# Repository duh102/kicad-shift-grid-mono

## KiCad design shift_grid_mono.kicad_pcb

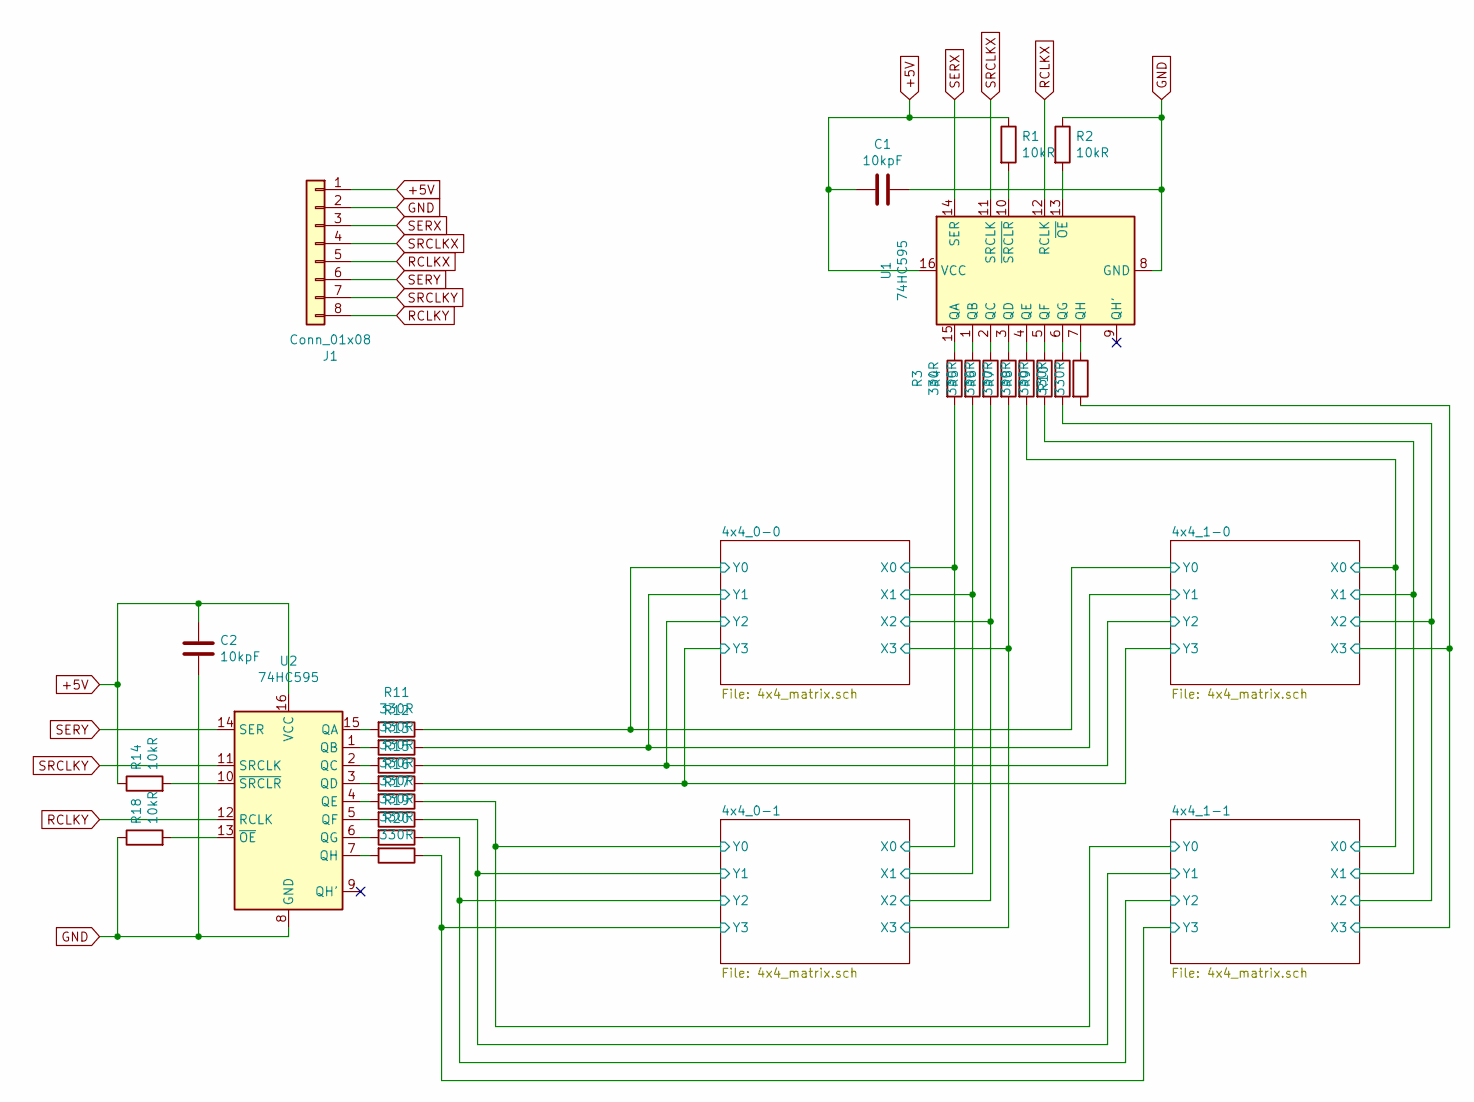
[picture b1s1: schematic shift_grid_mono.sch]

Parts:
C1, C2: 10kpF; C_0805_2012Metric
J1: Conn_01x08; PinHeader_1x08_P2.54mm_Vertical
R1, R2, R14, R18: 10kR; R_0805_2012Metric
R3, R4, R5, R6, R7, R8, R9, R10, R11, R12, R13, R15, R16, R17, R19, R20: 330R; R_0805_2012Metric
U1, U2: 74HC595; SOIC-16_3.9x9.9mm_P1.27mm

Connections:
+5V: C1.2, C2.1, J1.1, R1.1, R14.1, U1.16 (VCC), U2.16 (VCC)
/4x4_0-0/X0: R3.2; also elsewhere on the board
/4x4_0-0/X1: R4.2; also elsewhere on the board
/4x4_0-0/X2: R5.2; also elsewhere on the board
/4x4_0-0/X3: R6.2; also elsewhere on the board
/4x4_0-0/Y0: R11.1; also elsewhere on the board
/4x4_0-0/Y1: R12.1; also elsewhere on the board
/4x4_0-0/Y2: R13.1; also elsewhere on the board
/4x4_0-0/Y3: R15.1; also elsewhere on the board
/4x4_0-1/Y0: R16.1; also elsewhere on the board
/4x4_0-1/Y1: R17.1; also elsewhere on the board
/4x4_0-1/Y2: R19.1; also elsewhere on the board
/4x4_0-1/Y3: R20.1; also elsewhere on the board
/4x4_1-0/X0: R7.2; also elsewhere on the board
/4x4_1-0/X1: R8.2; also elsewhere on the board
/4x4_1-0/X2: R9.2; also elsewhere on the board
/4x4_1-0/X3: R10.2; also elsewhere on the board
GND: C1.1, C2.2, J1.2, R2.1, R18.1, U1.8 (GND), U2.8 (GND)
unnamed: R1.2, U1.10 (~SRCLR)
unnamed: R2.2, U1.13 (~OE)
unnamed: R3.1, U1.15 (QA)
unnamed: R4.1, U1.1 (QB)
unnamed: R5.1, U1.2 (QC)
unnamed: R6.1, U1.3 (QD)
unnamed: R7.1, U1.4 (QE)
unnamed: R8.1, U1.5 (QF)
unnamed: R9.1, U1.6 (QG)
unnamed: R10.1, U1.7 (QH)
unnamed: R11.2, U2.15 (QA)
unnamed: R12.2, U2.1 (QB)
unnamed: R13.2, U2.2 (QC)
unnamed: R14.2, U2.10 (~SRCLR)
unnamed: R15.2, U2.3 (QD)
unnamed: R16.2, U2.4 (QE)
unnamed: R17.2, U2.5 (QF)
unnamed: R18.2, U2.13 (~OE)
unnamed: R19.2, U2.6 (QG)
unnamed: R20.2, U2.7 (QH)
RCLKX: J1.5, U1.12 (RCLK)
RCLKY: J1.8, U2.12 (RCLK)
SERX: J1.3, U1.14 (SER)
SERY: J1.6, U2.14 (SER)
SRCLKX: J1.4, U1.11 (SRCLK)
SRCLKY: J1.7, U2.11 (SRCLK)

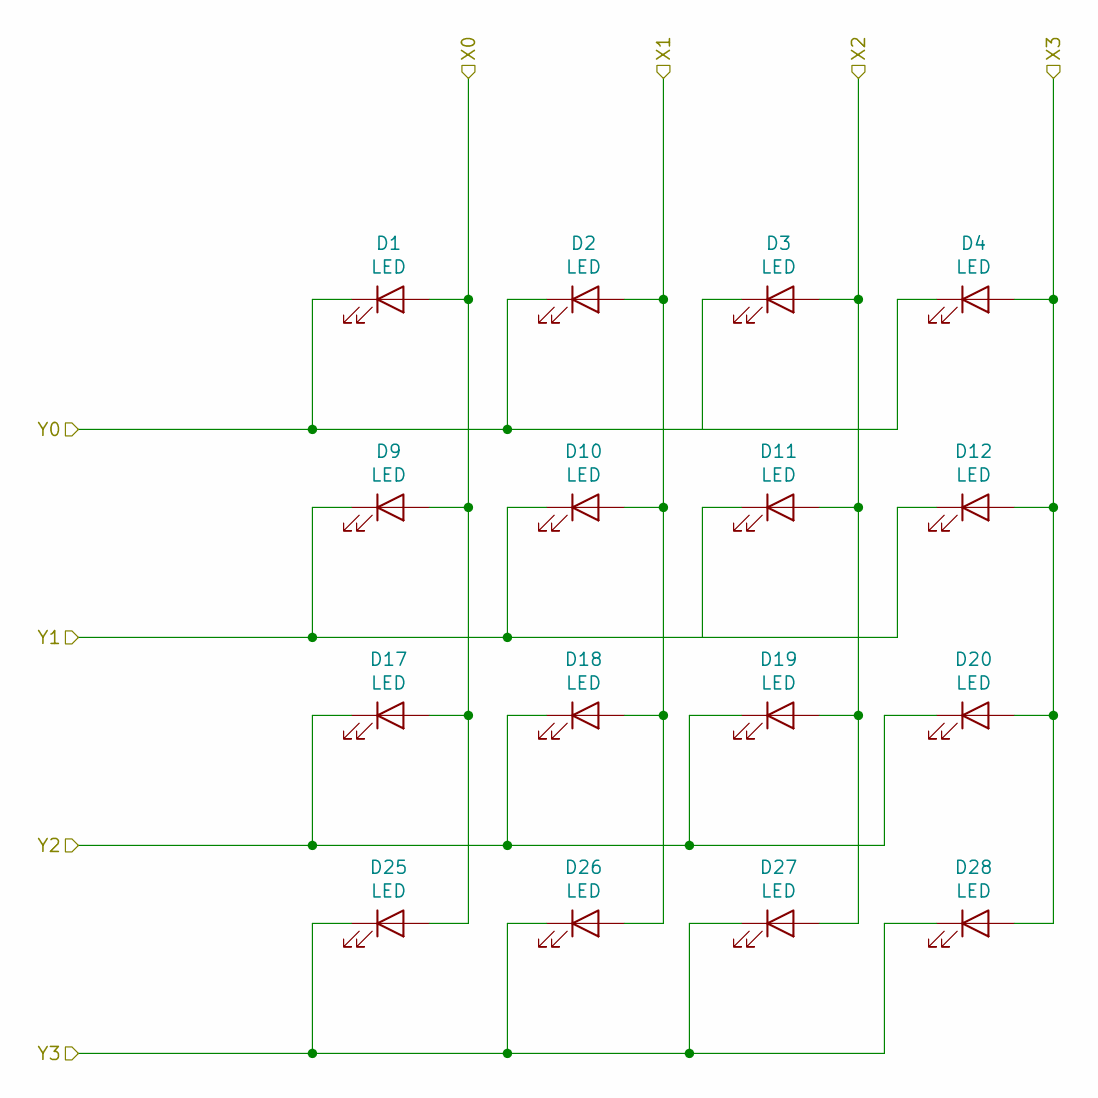
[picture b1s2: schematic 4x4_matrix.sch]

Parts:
D1, D2, D3, D4, D9, D10, D11, D12, D17, D18, D19, D20, D25, D26, D27, D28: LED; LED_0805_2012Metric

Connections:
/4x4_0-0/X0: D1.2 (A), D9.2 (A), D17.2 (A), D25.2 (A); also elsewhere on the board
/4x4_0-0/X1: D2.2 (A), D10.2 (A), D18.2 (A), D26.2 (A); also elsewhere on the board
/4x4_0-0/X2: D3.2 (A), D11.2 (A), D19.2 (A), D27.2 (A); also elsewhere on the board
/4x4_0-0/X3: D4.2 (A), D12.2 (A), D20.2 (A), D28.2 (A); also elsewhere on the board
/4x4_0-0/Y0: D1.1 (K), D2.1 (K), D3.1 (K), D4.1 (K); also elsewhere on the board
/4x4_0-0/Y1: D9.1 (K), D10.1 (K), D11.1 (K), D12.1 (K); also elsewhere on the board
/4x4_0-0/Y2: D17.1 (K), D18.1 (K), D19.1 (K), D20.1 (K); also elsewhere on the board
/4x4_0-0/Y3: D25.1 (K), D26.1 (K), D27.1 (K), D28.1 (K); also elsewhere on the board

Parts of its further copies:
D33, D34, D35, D36, D41, D42, D43, D44, D49, D50, D51, D52, D57, D58, D59, D60, D65, D66, D67, D68, D73, D74, D75, D76, D81, D82, D83, D84, D89, D90, D91, D92, D97, D98, D99, D100, D105, D106, D107, D108, D113, D114, D115, D116, D121, D122, D123, D124: LED; LED_0805_2012Metric

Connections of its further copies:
/4x4_0-0/X0: D33.2 (A), D41.2 (A), D49.2 (A), D57.2 (A); also elsewhere on the board
/4x4_0-0/X1: D34.2 (A), D42.2 (A), D50.2 (A), D58.2 (A); also elsewhere on the board
/4x4_0-0/X2: D35.2 (A), D43.2 (A), D51.2 (A), D59.2 (A); also elsewhere on the board
/4x4_0-0/X3: D36.2 (A), D44.2 (A), D52.2 (A), D60.2 (A); also elsewhere on the board
/4x4_0-0/Y0: D65.1 (K), D66.1 (K), D67.1 (K), D68.1 (K); also elsewhere on the board
/4x4_0-0/Y1: D73.1 (K), D74.1 (K), D75.1 (K), D76.1 (K); also elsewhere on the board
/4x4_0-0/Y2: D81.1 (K), D82.1 (K), D83.1 (K), D84.1 (K); also elsewhere on the board
/4x4_0-0/Y3: D89.1 (K), D90.1 (K), D91.1 (K), D92.1 (K); also elsewhere on the board
/4x4_0-1/Y0: D33.1 (K), D34.1 (K), D35.1 (K), D36.1 (K), D97.1 (K), D98.1 (K), D99.1 (K), D100.1 (K); also elsewhere on the board
/4x4_0-1/Y1: D41.1 (K), D42.1 (K), D43.1 (K), D44.1 (K), D105.1 (K), D106.1 (K), D107.1 (K), D108.1 (K); also elsewhere on the board
/4x4_0-1/Y2: D49.1 (K), D50.1 (K), D51.1 (K), D52.1 (K), D113.1 (K), D114.1 (K), D115.1 (K), D116.1 (K); also elsewhere on the board
/4x4_0-1/Y3: D57.1 (K), D58.1 (K), D59.1 (K), D60.1 (K), D121.1 (K), D122.1 (K), D123.1 (K), D124.1 (K); also elsewhere on the board
/4x4_1-0/X0: D65.2 (A), D73.2 (A), D81.2 (A), D89.2 (A), D97.2 (A), D105.2 (A), D113.2 (A), D121.2 (A); also elsewhere on the board
/4x4_1-0/X1: D66.2 (A), D74.2 (A), D82.2 (A), D90.2 (A), D98.2 (A), D106.2 (A), D114.2 (A), D122.2 (A); also elsewhere on the board
/4x4_1-0/X2: D67.2 (A), D75.2 (A), D83.2 (A), D91.2 (A), D99.2 (A), D107.2 (A), D115.2 (A), D123.2 (A); also elsewhere on the board
/4x4_1-0/X3: D68.2 (A), D76.2 (A), D84.2 (A), D92.2 (A), D100.2 (A), D108.2 (A), D116.2 (A), D124.2 (A); also elsewhere on the board

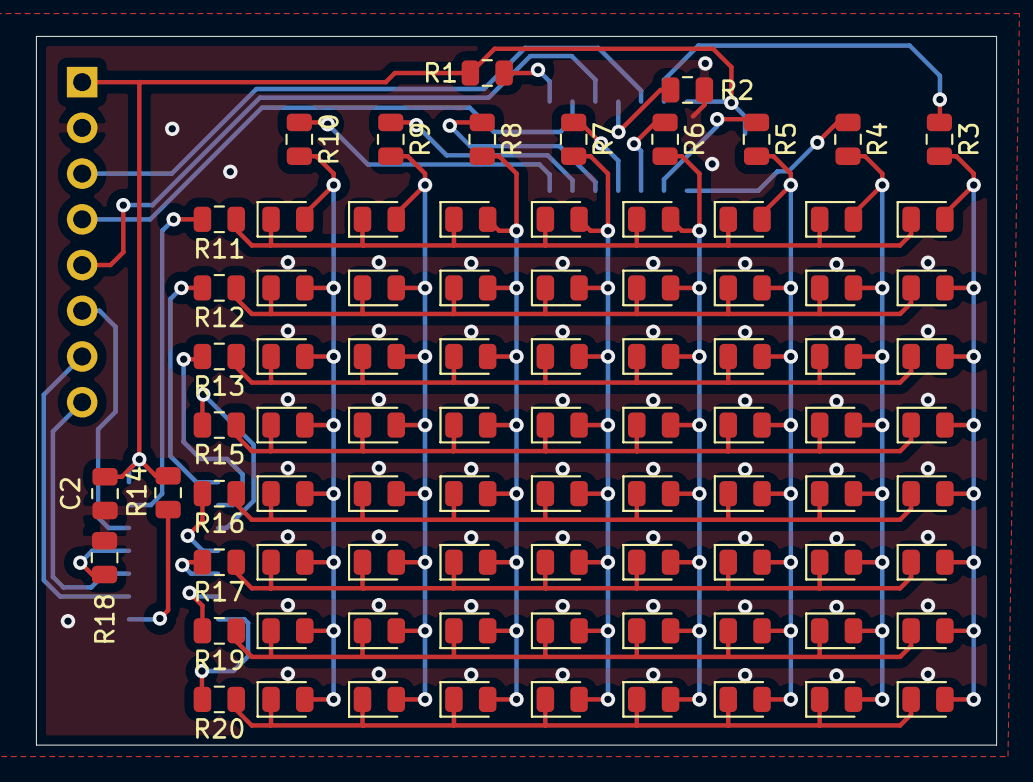
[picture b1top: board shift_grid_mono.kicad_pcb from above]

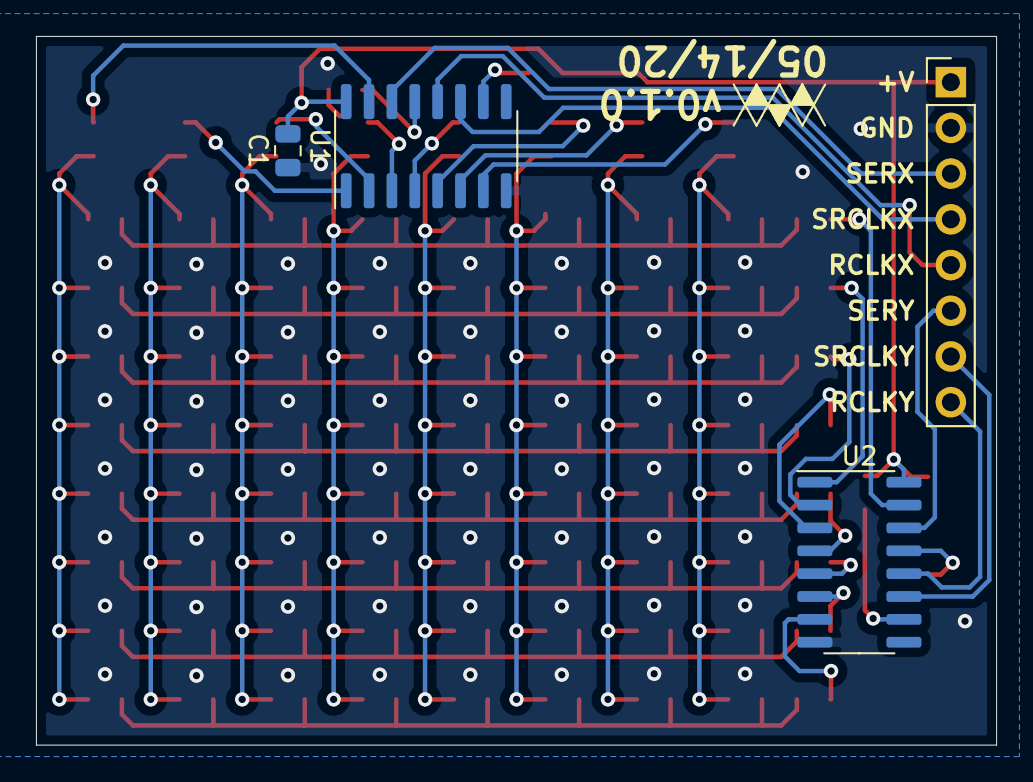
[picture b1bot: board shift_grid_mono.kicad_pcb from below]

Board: 2 copper layers, 53.3 x 39.4 mm, 89 parts (4 on the bottom side), 44 nets.

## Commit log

2020-05-09 Fix messed up rows 3,4
2020-05-15 Reduce LEDs by half
2020-05-18 Correct modify time
